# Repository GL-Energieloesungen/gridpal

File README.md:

# Project Overview
GL Energy Cloud 2.0 was developed as an intelligent measurement and analysis system and offers real added value compared to conventional monitoring systems. The core competence of this solution is the collection of energy consumption data, the secure transmission of this data to a central server and the subsequent application of various, more efficient data analysis techniques to depict energy flows. The system can be used both in companies and in public buildings (e.g. administrative buildings, sports facilities, etc.). With the GL Energy Cloud 2.0 it is possible to identify energy efficiency potential or to check the success of implemented energy efficiency measures. The system includes both a hardware and a software solution.

## Data Collection 
The GL Energy Cloud 2.0 supports various wired and wireless communication protocols to allow a broad application for data logging and controlling functions. It facilitates the logging of any environmental, consumption, user or status data via connected devices such as meters and sensors (for continuous measurement), actors or programmable controllers (SPS). It also supports the control of such connected devices through its on-/offboard interfaces/protocols. Currently Supported interfaces to collect data are

- ModBus
- Mbus
- Wireless Mbus
- KNX

Bellow are the details of the hardware and interfaces

- Mainboard: Quad-Core ARM Cortex A53 Processor (64bit),Built-in Crypto-Engine, Ethernet 10/100/1000 Mbps (see Allwinner A64 documentation)
- Supplemental PCB board: Bluetooth Low Energy (BLE, 4.2 compliant), LAN min. 2x Gigabit Ethernet, Wifi 802.11n 2.4GhZ / 802.11ac 5 Ghz, 1x Modbus RS485 connector, 1x M-bus connector, 1x wireless M-bus, 1x KNX/EIB connector
- Peripherals: 4x USB (1x external, 3x internal), UART / PIN connector, SD Card slot, Smart Card slot (encryption private key)
- Connectivity (offboard, optional via USB dongles): LTE Modem, ZigBee, Enocean, Z-Wafe, Q-Wave
- Connectivity (offboard, optional via separate PCB Board on PIN Interface): PCB Board with MCU, 2x S0 analogue Input (Impulse), 4x analogue   Input for Sensor Typs KTY (2 kΩ) and PT1000, 4x analogue Input 0-10V (1 mA), 4x analogue Output (opener/ closer relais potentialfree), 4x analogue Output 0-10V (1 mA) switchable to PWM
- Operating System: LINUX full distribution (headless), support for JAVA, Pythoon

## Data Transfer
The GL Energy Cloud 2.0 uses mqtt as the transfer mechanism to transfer the collected data to a distributed mqtt broker.

## Data analysis
The GL Energy Cloud 2.0 can provide data feed to any third party data analysis tool

## Hardware
All the schematics and pcb layout are designed in Kicad, an open source Electronic Design Automation (EDA) tool https://www.kicad.org/

There are 2 PCBA to be manufactured

- [Com Board](Hardware/Com%20Board)
- [Main Board](Hardware/Main%20Board)
    
To Manufacture the PCBA you have to open the respective folders in kicad tool and have to generate the gerber files for each board.
One can easily follow kicad tool's documentation to generate the gerber. For [example](https://support.jlcpcb.com/article/44-how-to-export-kicad-pcb-to-gerber-files) 
    
## Software
Software is consist of following parts. Each part has their own documentation to build them from their repective source code
- [Operating System](Software/OS)
- [Application Program](Software/APPS)
- [Graphical User Interface](Software/GUI/gridpal-ui)

## Pre-built Linux image
For convenience a stable linux image is pre-built in this [link](https://drive.google.com/drive/folders/1ytiXBGopky1tuhhxSThNLuGj5j8QVbeQ)

All the applications, GUI on top of the linux image is prebuilt inside the image.

## Installing Linux Image to a SD card
- Download the prebuilt [linux image](https://drive.google.com/drive/folders/1ytiXBGopky1tuhhxSThNLuGj5j8QVbeQ)
- Grab a SD card (at lease 32 GB)
- Install [Etcher software](https://www.balena.io/etcher) in a PC
- Then burn the image to sd card using the Etcher software
- Insert the sd card in the [Main Board](Hardware/Main%20Board)

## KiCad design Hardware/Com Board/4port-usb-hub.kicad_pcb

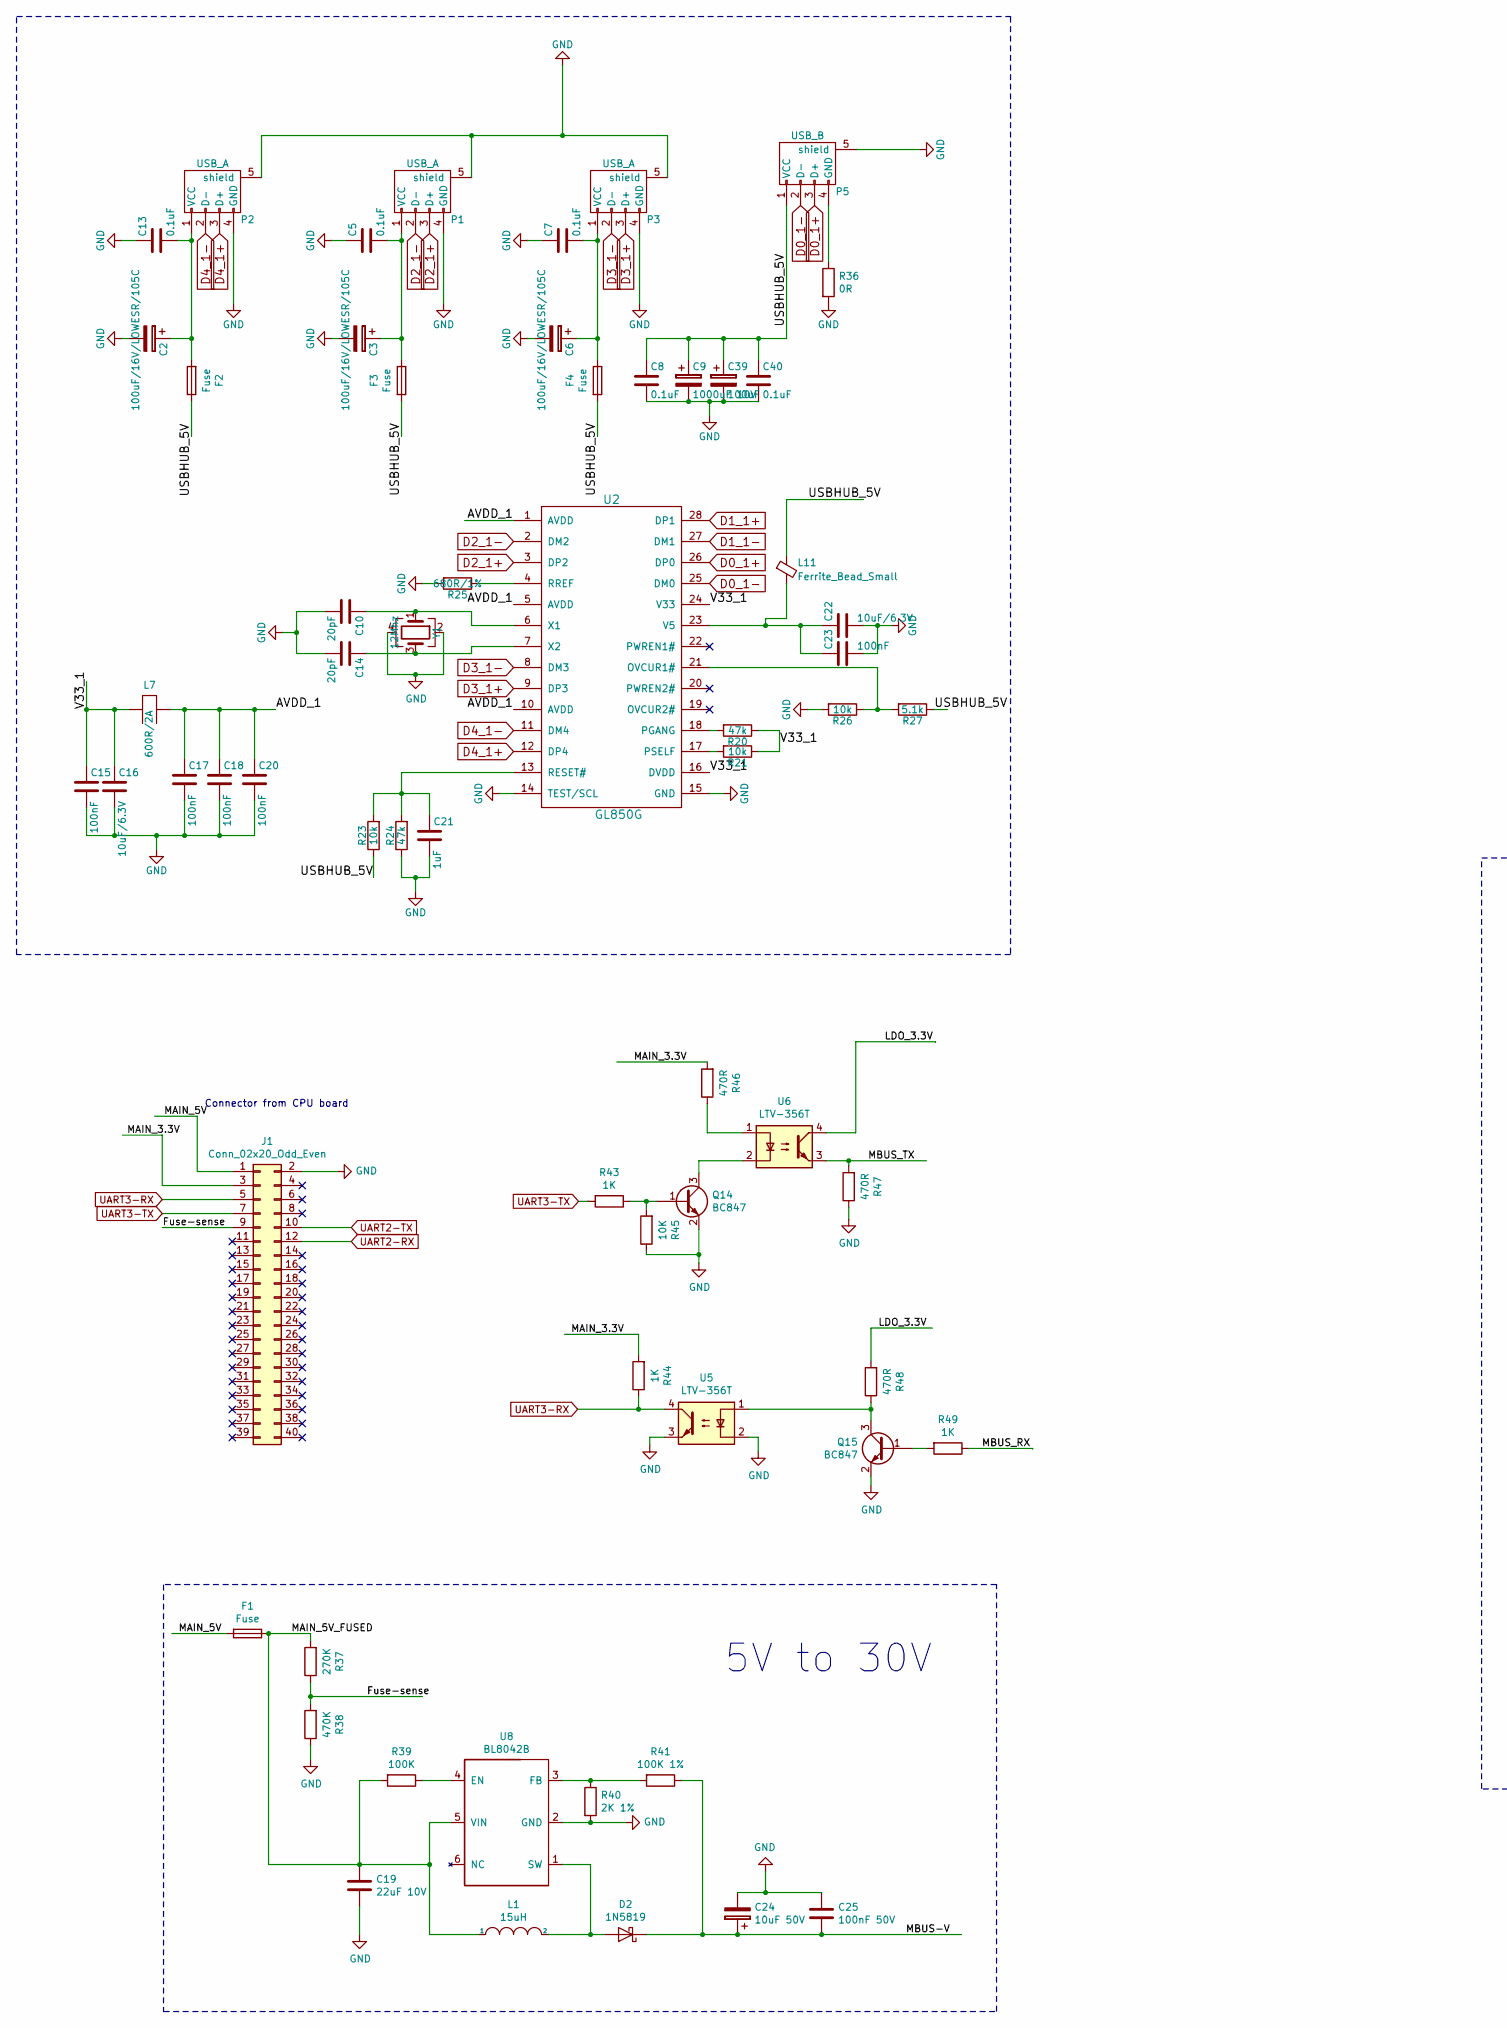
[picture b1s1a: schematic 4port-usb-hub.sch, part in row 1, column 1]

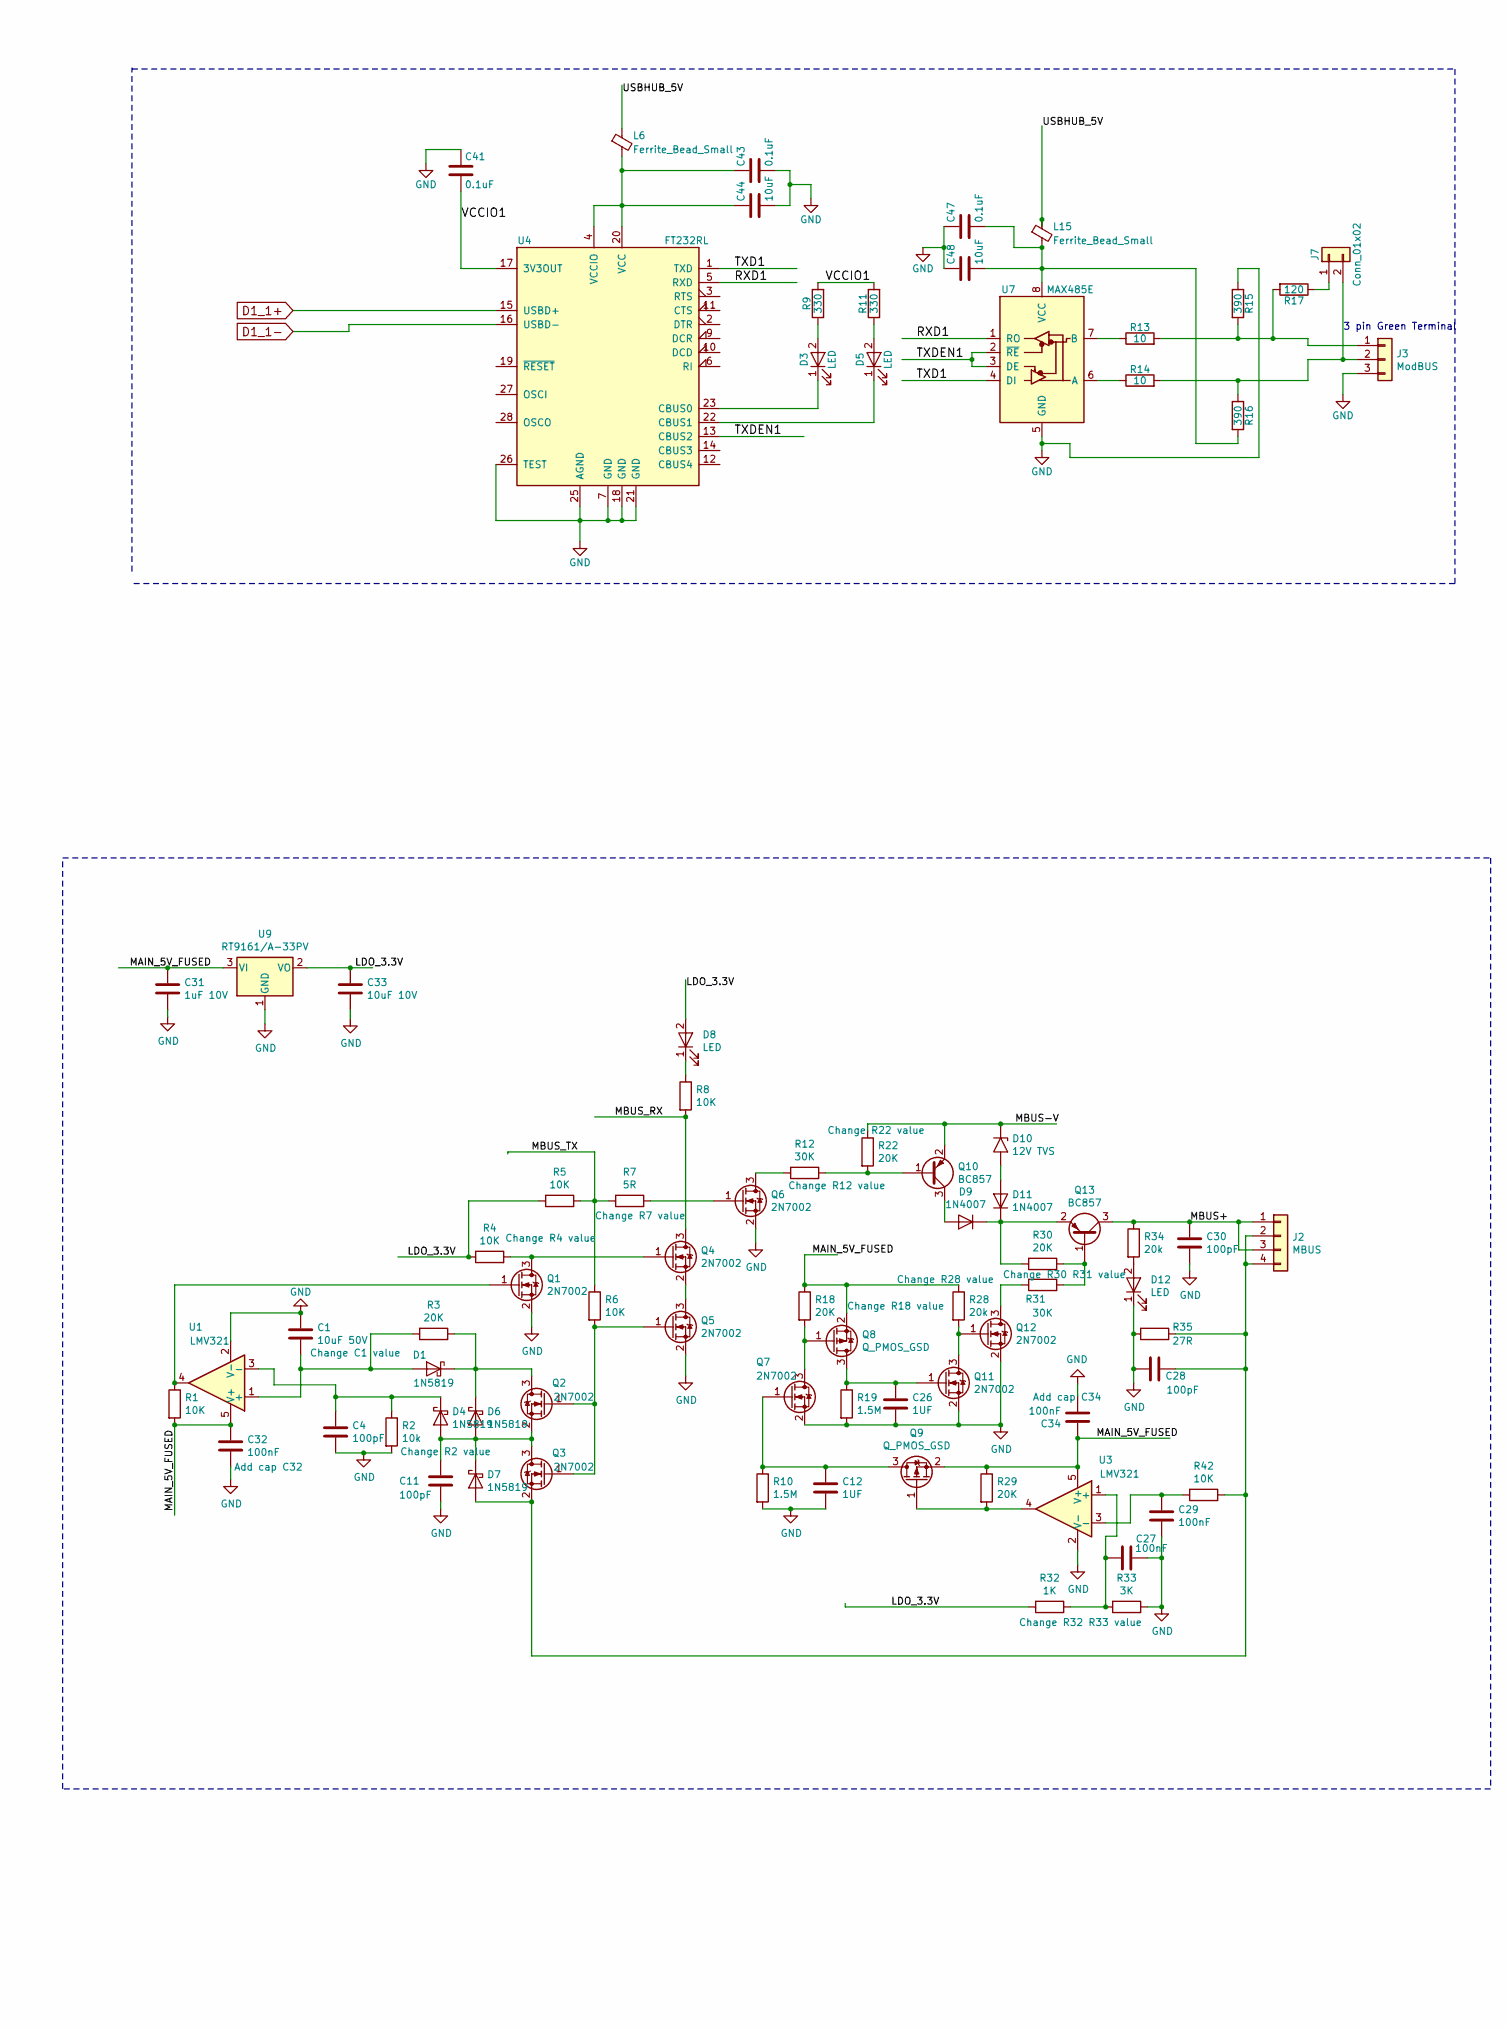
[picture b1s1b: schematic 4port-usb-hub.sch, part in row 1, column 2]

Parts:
C1: 10uF 50V; C_0805
C2, C3, C6: 100uF/16V/LOWESR/105C; CP_Elec_6.3x5.3
C4, C11, C28, C30: 100pF; C_0603
C5, C7, C8, C13, C40, C41, C43, C47: 0.1uF; C_0603
C9: 1000uF 10V; CP_Elec_10x10.5
C10, C14: 20pF; C_0603
C12, C26: 1UF; C_0603
C15, C17, C18, C20, C23, C27, C29, C32, C34: 100nF; C_0603
C16, C22: 10uF/6.3V; C_0603
C19: 22uF 10V; C_1206
C21: 1uF; C_0603
C24: 10uF 50V; CP_Elec_5x5.3
C25: 100nF 50V; C_0603
C31: 1uF 10V; C_0805
C33: 10uF 10V; C_0805
C39: 100uF; CP_Elec_6.3x4.5
C44, C48: 10uF; C_0603
D1, D4, D6, D7: 1N5819; D_SOD-323
D2: 1N5819; D_SOD-123
D3, D5: LED; LED_0603_HandSoldering
D8, D12: LED; LED_0805
D9, D11: 1N4007; D_SMA
D10: 12V TVS; D_SMA
F1, F2, F3, F4: Fuse; Fuse_SMD1206_Reflow
J1: Conn_02x20_Odd_Even; Pin_Header_Straight_2x20_Pitch2.54mm
J2: MBUS; JST_NV_B04P-NV_4x5.00mm_Vertical
J3: ModBUS; JST_NV_B03P-NV_3x5.00mm_Vertical
J7: Conn_01x02; Pin_Header_Straight_1x02_Pitch2.54mm
L1: 15uH; L_Taiyo-Yuden_MD-5050
L6, L11, L15: Ferrite_Bead_Small; L_0805
L7: 600R/2A; L_0805
P1, P2, P3: USB_A; USB_A_Vertical
P5: USB_B; USB_DIP
Q1, Q2, Q3, Q4, Q5, Q6, Q7, Q11, Q12: 2N7002; SOT-23
Q8, Q9: Q_PMOS_GSD; SOT-23
Q10, Q13: BC857; SOT-23
Q14, Q15: BC847; SOT-23
R1, R4, R5, R6, R8, R42, R45: 10K; R_0603
R2, R21, R23, R26: 10k; R_0603
R3, R18, R22, R29, R30: 20K; R_0603
R7: 5R; R_0603
R9, R11: 330; R_0603
R10, R19: 1.5M; R_0603
R12, R31: 30K; R_0603
R13, R14: 10; R_0603
R15, R16: 390; R_0603
R17: 120; R_0603
R20, R24: 47k; R_0603
R25: 680R/1%; R_0603
R27: 5.1k; R_0603
R28, R34: 20k; R_0603
R32, R43, R44, R49: 1K; R_0603
R33: 3K; R_0603
R35: 27R; R_2512
R36: 0R; R_0603
R37: 270K; R_0603
R38: 470K; R_0603
R39: 100K; R_0603
R40: 2K 1%; R_0603
R41: 100K 1%; R_0603
R46, R47, R48: 470R; R_0603
U1, U3: LMV321; SOT-23-5
U2: GL850G; SSOP-28_5.3x10.2mm_Pitch0.65mm
U4: FT232RL; SSOP-28_5.3x10.2mm_Pitch0.65mm
U5, U6: LTV-356T
U7: MAX485E; SOIC-8_3.9x4.9mm_Pitch1.27mm
U8: BL8042B; SOT-23-6
U9: RT9161/A-33PV; SOT-23
Y1: 12Mhz; Crystal_SMD_3225-4pin_3.2x2.5mm

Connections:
/AVDD_1: C17.1, C18.1, C20.1, L7.2, U2.1 (AVDD), U2.5 (AVDD), U2.10 (AVDD)
/Fuse-sense: J1.9, R37.1, R38.2
/LDO_3.3V: C33.1, D8.2 (A), R4.1, R5.2, R32.2, R48.2, U6.4, U9.2 (VO)
/MAIN_3.3V: J1.3, R44.2, R46.2
/MAIN_5V: F1.2, J1.1
/MAIN_5V_FUSED: C19.1, C31.1, C32.1, C34.1, F1.1, L1.1, Q8.2 (S), Q9.2 (S), R1.2, R18.1, R28.1, R29.1, R37.2, R39.2, U1.5 (V+), U3.5 (V+), U8.5 (VIN), U9.3 (VI)
/MBUS+: C30.1, J2.1, J2.3, Q13.3 (C), R34.1
/MBUS-V: C24.1, C25.2, D2.1 (K), D10.1 (A1), Q10.2 (E), R22.1, R41.1
/MBUS_RX: Q4.3 (D), R8.2, R49.1
/MBUS_TX: R5.1, R6.1, R7.2, R47.2, U6.3
/RXD1: U4.5 (RXD), U7.1 (RO)
/TXD1: U4.1 (TXD), U7.4 (DI)
/TXDEN1: U4.13 (CBUS2), U7.2 (~RE), U7.3 (DE)
/USBHUB_5V: C8.1, C9.1, C39.1, C40.1, F2.1, F3.2, F4.2, L6.1, L11.1, L15.1, P5.1 (VCC), R23.1, R27.1
/V33_1: C15.1, C16.1, L7.1, R20.1, R21.1, U2.16 (DVDD), U2.24 (V33)
/VCCIO1: C41.2, R9.2, R11.2, U4.17 (3V3OUT)
D0_1+: P5.3 (D+), U2.26 (DP0)
D0_1-: P5.2 (D-), U2.25 (DM0)
D1_1+: U2.28 (DP1), U4.15 (USBD+)
D1_1-: U2.27 (DM1), U4.16 (USBD-)
D2_1+: P1.3 (D+), U2.3 (DP2)
D2_1-: P1.2 (D-), U2.2 (DM2)
D3_1+: P3.3 (D+), U2.9 (DP3)
D3_1-: P3.2 (D-), U2.8 (DM3)
D4_1+: P2.3 (D+), U2.12 (DP4)
D4_1-: P2.2 (D-), U2.11 (DM4)
GND: C1.1, C2.2, C3.2, C4.2, C5.1, C6.2, C7.1, C8.2, C9.2, C10.2, C11.2, C12.2, C13.1, C14.2, C15.2, C16.2, C17.2, C18.2, C19.2, C20.2, C21.2, C22.2, C23.2, C24.2, C25.1, C26.2, C27.1, C28.2, C29.2, C30.2, C31.2, C32.2, C33.2, C34.2, C39.2, C40.2, C41.1, C43.2, C44.2, C47.1, C48.1, D12.1 (K), J1.2, J3.3, P1.4 (GND), P1.5 (shield), P2.4 (GND), P2.5 (shield), P3.4 (GND), P3.5 (shield), P5.5 (shield), Q1.2 (S), Q5.2 (S), Q6.2 (S), Q7.2 (S), Q11.2 (S), Q12.2 (S), Q14.2 (E), Q15.2 (E), R2.2, R10.2, R15.1, R19.2, R24.1, R25.2, R26.2, R33.1, R35.2, R36.2, R38.1, R40.2, R45.1, R47.1, U1.2 (V-), U2.14 (TEST/SCL), U2.15 (GND), U3.2 (V-), U4.7 (GND), U4.18 (GND), U4.21 (GND), U4.25 (AGND), U4.26 (TEST), U5.2, U5.3, U7.5 (GND), U8.2 (GND), U9.1 (GND), Y1.2, Y1.4
unnamed: C1.2, D1.2 (A), R3.2, U1.1 (+)
unnamed: C3.1, C5.2, F3.1, P1.1 (VCC)
unnamed: C4.1, D4.1 (K), R2.1, U1.3 (-)
unnamed: C6.1, C7.2, F4.1, P3.1 (VCC)
unnamed: C10.1, U2.6 (X1), Y1.1
unnamed: C11.1, D4.2 (A), D6.2 (A), D7.1 (K), Q2.2 (S), Q3.3 (D)
unnamed: C12.1, Q7.1 (G), Q9.3 (D), R10.1
unnamed: C2.1, C13.2, F2.2, P2.1 (VCC)
unnamed: C14.1, U2.7 (X2), Y1.3
unnamed: C21.1, R23.2, R24.2, U2.13 (RESET#)
unnamed: C22.1, C23.1, L11.2, U2.23 (V5)
unnamed: C26.1, Q8.3 (D), Q11.1 (G), R19.1
unnamed: C27.2, R32.1, R33.2, U3.1 (+)
unnamed: C28.1, D7.2 (A), J2.2, J2.4, Q3.2 (S), R35.1, R42.1
unnamed: C29.1, R42.2, U3.3 (-)
unnamed: C43.1, C44.1, L6.2, U4.4 (VCCIO), U4.20 (VCC)
unnamed: C47.2, C48.2, L15.2, R16.2, U7.8 (VCC)
unnamed: D1.1 (K), D6.1 (K), Q2.3 (D), R3.1
unnamed: D2.2 (A), L1.2, U8.1 (SW)
unnamed: D3.1 (K), U4.23 (CBUS0)
unnamed: D3.2 (A), R9.1
unnamed: D5.1 (K), U4.22 (CBUS1)
unnamed: D5.2 (A), R11.1
unnamed: D8.1 (K), R8.1
unnamed: D9.2 (A), Q10.3 (C)
unnamed: D10.2 (A2), D11.2 (A)
unnamed: D9.1 (K), D11.1 (K), Q13.2 (E), R30.2
unnamed: D12.2 (A), R34.2
unnamed: J3.1, R13.2, R15.2, R17.2
unnamed: J3.2, J7.2, R14.2, R16.1
unnamed: J7.1, R17.1
unnamed: P5.4 (GND), R36.1
unnamed: Q1.1 (G), R1.1, U1.4
unnamed: Q1.3 (D), Q4.1 (G), R4.2
unnamed: Q2.1 (G), Q3.1 (G), Q5.1 (G), R6.2
unnamed: Q4.2 (S), Q5.3 (D)
unnamed: Q6.1 (G), R7.1
unnamed: Q6.3 (D), R12.2
unnamed: Q7.3 (D), Q8.1 (G), R18.2
unnamed: Q9.1 (G), R29.2, U3.4
unnamed: Q10.1 (B), R12.1, R22.2
unnamed: Q11.3 (D), Q12.1 (G), R28.2
unnamed: Q12.3 (D), R31.2
unnamed: Q13.1 (B), R30.1, R31.1
unnamed: Q14.1 (B), R43.1, R45.2
unnamed: Q14.3 (C), U6.2
unnamed: Q15.1 (B), R49.2
unnamed: Q15.3 (C), R48.1, U5.1
unnamed: R13.1, U7.7 (B)
unnamed: R14.1, U7.6 (A)
unnamed: R20.2, U2.18 (PGANG)
unnamed: R21.2, U2.17 (PSELF)
unnamed: R25.1, U2.4 (RREF)
unnamed: R26.1, R27.2, U2.21 (OVCUR1#)
unnamed: R39.1, U8.4 (EN)
unnamed: R40.1, R41.2, U8.3 (FB)
unnamed: R46.1, U6.1
UART2-RX: J1.12
UART2-TX: J1.10
UART3-RX: J1.5, R44.1, U5.4
UART3-TX: J1.7, R43.2

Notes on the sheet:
3 pin Green Terminal
Connector from CPU board
5V to 30V

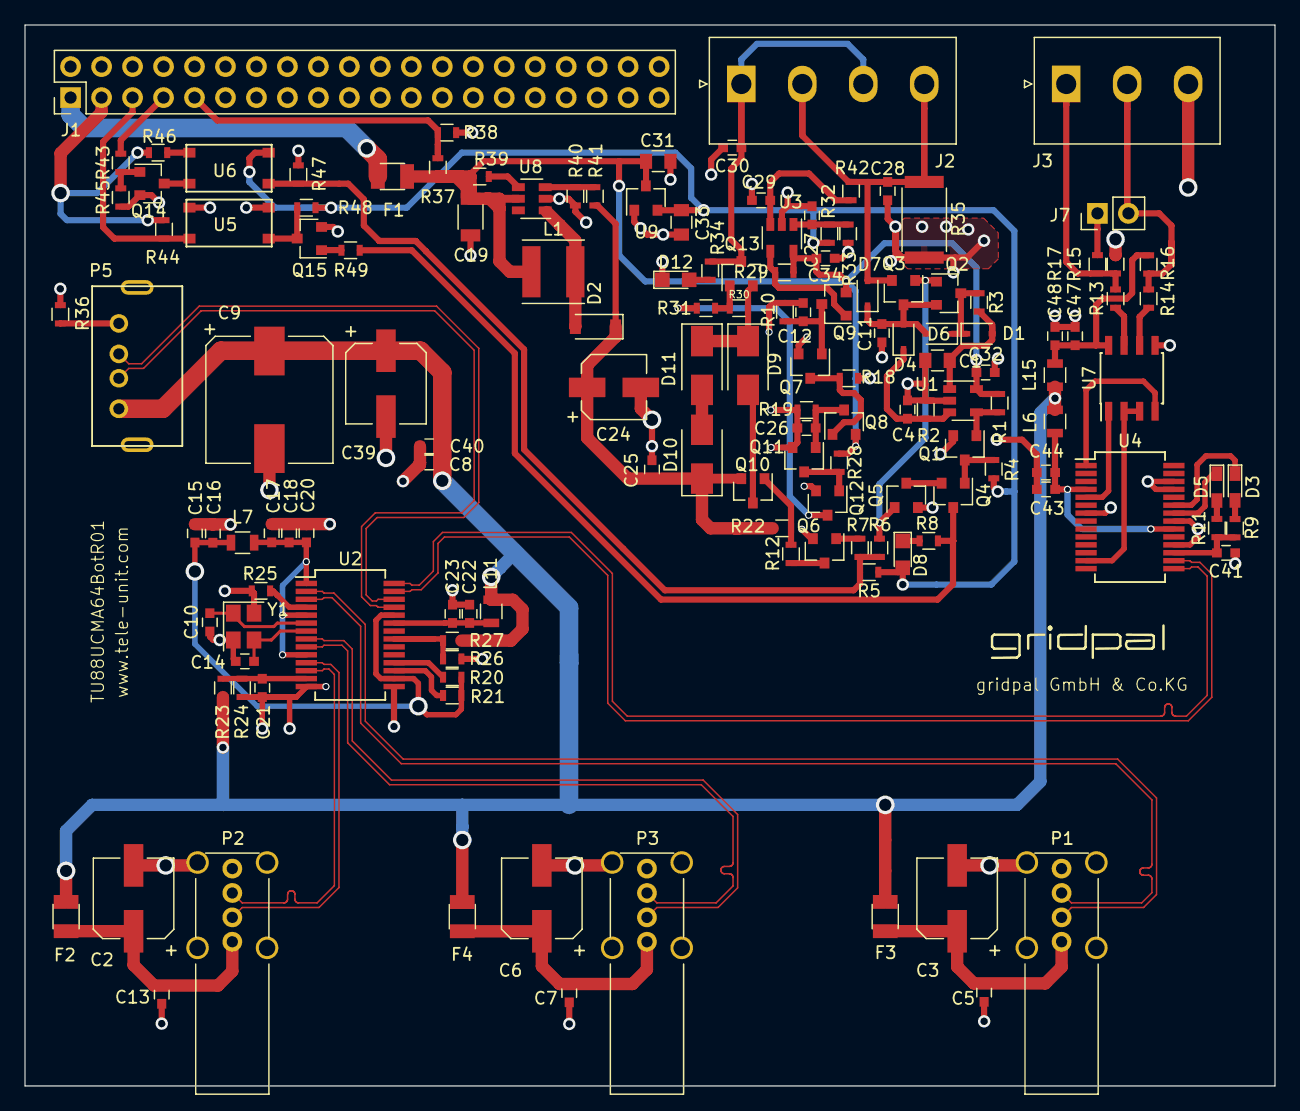
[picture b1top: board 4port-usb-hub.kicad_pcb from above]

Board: 2 copper layers, 102.5 x 87.0 mm, 144 parts (0 on the bottom side), 86 nets.

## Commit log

2022-01-23 add stable os image
2022-01-25 OS image files removed
2022-01-25 OS Image links provided
2022-01-25 OS Image correct links provided
2022-02-15 Readme file edited
2022-03-21 more documentation added
2023-02-24 Update README.md
    Hardware generation doc updated
2023-02-24 Update README.md
    More updated readme
2023-02-24 Update README.md
    More changes
